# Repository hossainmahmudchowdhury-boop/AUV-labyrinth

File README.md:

# AUV-labyrinth

#### Outlook

This project is about an underwater submarine that can follow a route to survey the aquatic environment. It can detect the number of fish in an area and observe aquatic biology. In this project, it emphasizes an ML-based detection system and a water quality checker.

### PCB 

## Bill of Materials (BOM)

The following table lists the estimated components and costs for the underwater surveillance submarine prototype. The system combines onboard image processing, sensor data collection, underwater imaging, and remote communication.

### 1. Mechanical and PCB Fabrication

| Category | Component | Description | Estimated Cost (USD) |
|---|---|---|---:|
| Mechanical | Waterproof 3D Printing | Custom submarine body | $125.00 |
| PCB Fabrication | Custom Motherboard | Main PCB with replaceable Raspberry Arduino nano headers, power regulation, and sensor interfaces | $58.00 |
| **Subtotal** | | | **$183.00** |

### 2. Electronics and Sensors

| Component | Specification / Purpose | Qty. | Unit Cost (USD) | Total (USD) | Link |
|---|---|---:|---:|---:|---:|
| Servo Motor | Servo rotation control | 6 | $7.40 | $44.40 | [Link](https://shorturl.at/46V4L) |
| Drive Motor | Propulsion | 1 | $46.00 | $46.00 | [Link](https://www.aliexpress.com/item/1005006684228018.html)|
|  CanMV K230 mini AI development board  | Image processing and onboard computing | 1 | $43.37  | $43.37  | [Link](https://www.aliexpress.com/item/1005008934429939.html)|
| Arduino Nano V3.0 Type C  | Sensor interfacing and data acquisition | 1 | $3.00 | $3.00 | [Link](https://www.aliexpress.com/item/1005011889513227.html)|
|  8x8 Thermal Imager Module | Thermal imaging for research | 1 | $32.08  | $32.08  | [Link](https://www.aliexpress.com/item/1005009168490634.html)|
| Gyro Sensor | 3-axis motion and orientation sensing | 1 | $9.51 | $9.51 | [Link](https://www.aliexpress.com/item/1005008666420561.html)|
| Lithium-ion Battery Bundle (20pcs) | Rechargeable power supply | 1 | $22.10 | $22.10 | [Link](https://www.aliexpress.com/item/1005006920168445.html)|
| Extension Cable | 20 m communication/data cable | 1 | $78.70 | $78.70 | [Link](https://www.aliexpress.com/item/1005012780715462.html)|
| Memory Card | 32 GB microSD card | 1 | $10.43  | $10.43  | [Link](https://www.aliexpress.com/item/1005007498167692.html)|
| Light/Infrared Color Spectrometer | Light measurement and spectral analysis | 1 | $8.01 | $8.01 | [Link](https://www.aliexpress.com/item/1005013219123992.html)|
| NEO-M8N GPS Module  |NEO-M8N GPS Module with Built-in Compass for APM PIX Pixhawk PX4|1 | $17.49 | $17.49 |  [Link](https://www.aliexpress.com/item/1005008748794240.html)|
| **Subtotal** | | | | **$315.90** |

### 3. Miscellaneous and Logistics

| Component | Description | Estimated Cost (USD) |
|---|---|---:|
| Passive Components and Hardware | Resistors, capacitors, connectors, and other miscellaneous parts | $15.00 |
| Shipping | Estimated shipping charges | $50.00 |
| **Subtotal** | | **$65.00** |

### 4. Estimated Project Cost

| Category | Estimated Cost (USD) |
|---|---:|
| Mechanical and PCB Fabrication | $183.00 |
| Electronics and Sensors | $315.90 |
| Miscellaneous and Shipping | $65.00 |
| **Total Estimated Cost** | **$563.90** |

> **Note:** All prices are approximate and may vary depending on supplier, availability, shipping, and import duties. Additional waterproof connectors, cable glands, motor drivers, battery protection, and pressure-resistant sealing may increase the final cost if they are not already included.

### 5. Mainboard Design Overview

The custom motherboard is designed around a removable Arduino Nano, connected through headers rather than permanently soldered to the PCB. The board is intended to provide:

- Sensor interfaces using I²C and SPI.
- MicroSD storage interface for sensor readings and other data the Pico can manage.
- USB/UART communication with external equipment.
- Gyroscope interface for motion and stability measurements.
- Motor-driver and servo-control connections.
- 5 V and 3.3 V power regulation.

**Design consideration:**

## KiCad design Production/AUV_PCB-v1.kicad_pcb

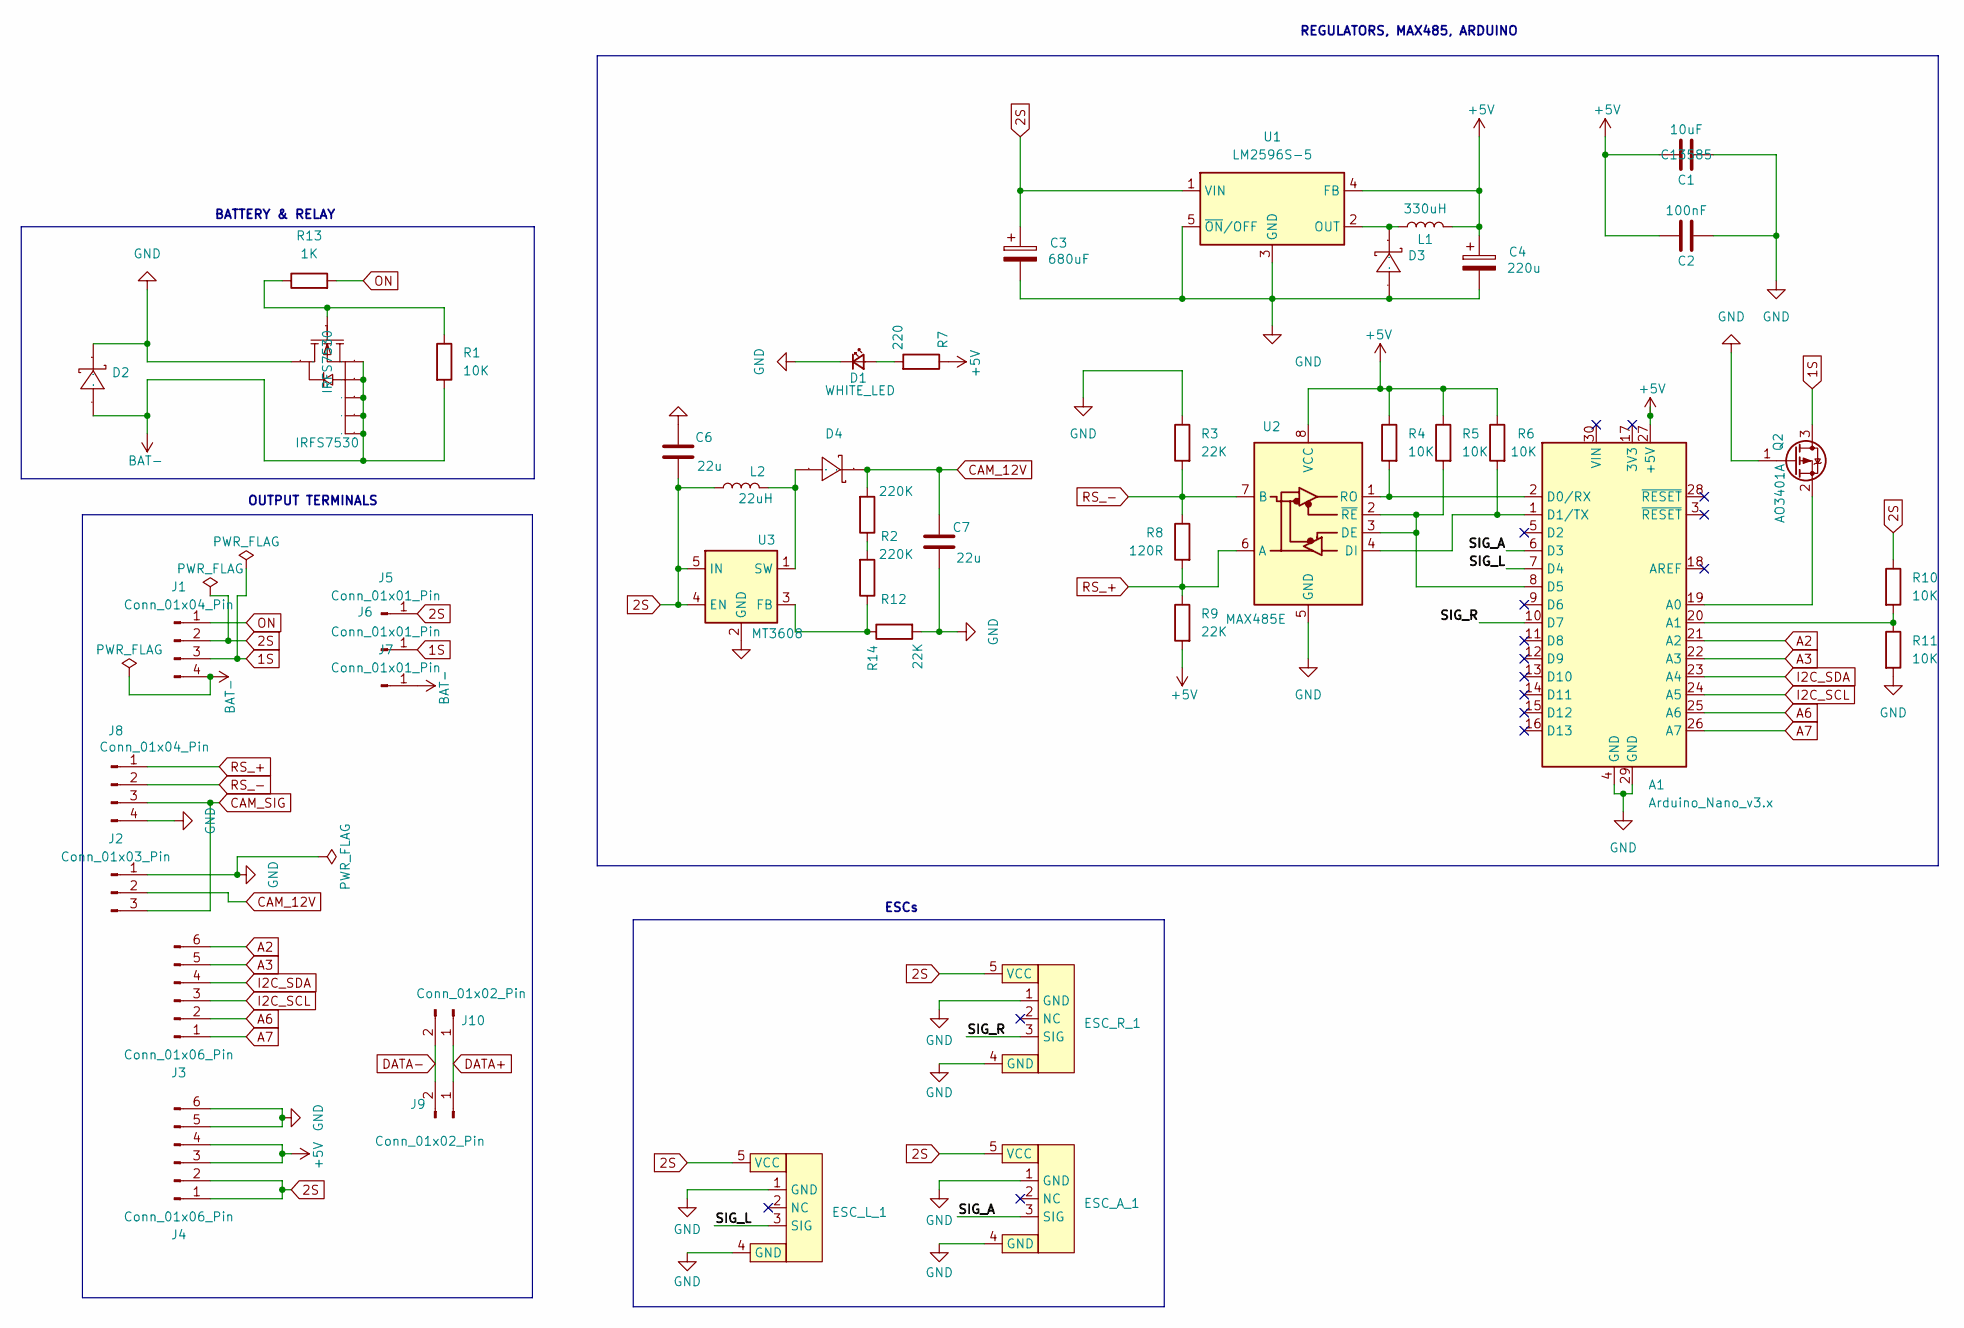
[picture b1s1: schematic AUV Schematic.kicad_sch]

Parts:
A1: Arduino_Nano_v3.x; Arduino_Nano
C1: 10uF; C_1206_3216Metric; LCSC C13585
C2: 100nF; C_0603_1608Metric; LCSC C24497
C3: 680uF; CP_Elec_10x10; LCSC C2980172
C4: 220u; CP_Elec_10x10; LCSC C125977
C6, C7: 22u; C_0805_2012Metric; LCSC C45783
D1: WHITE_LED; LED0603-RED
D2, D3, D4: SMA_L4.4-W2.8-LS5.4-RD; Manufacturer Part SS54; LCSC Part Name 电压:40V 电流:5A
ESC_A_1: ESC_BLHeli (20A), soldering
ESC_L_1: ESC_BLHeli (20A), soldering
ESC_R_1: ESC_BLHeli (20A), soldering
IRFS7530: IRFS7530; IRFS7530-D2PAK-7_L10.6-W9.6-P1.27-LS15.9-BR; LCSC Part Name C445669
J1, J8: Conn_01x04_Pin; PAD4
J2: Conn_01x03_Pin; PAD3
J3, J4: Conn_01x06_Pin; PAD6
J5, J7: Conn_01x01_Pin; Big_charging_pad
J6: Conn_01x01_Pin; small_charging_pad
J9: Conn_01x02_Pin; PAD2
J10: Conn_01x02_Pin; PAD2_rounded
L1: 330uH; L_12x12mm_H8mm; LCSC C10152
L2: 22uH; IND-SMD_L5.0-W3.8 REMOTE; LCSC C177244
Q2: AO3401A; SOT-23
R1: 10K; R_0402_1005Metric
R2: 220K; R_0603_1608Metric; LCSC C25905
R3: 22K; R_0402_1005Metric; LCSC C25768
R4, R5, R6, R10, R11: 10K; R_0402_1005Metric; LCSC C25744
R7: 220; R_0402_1005Metric; LCSC C25905
R8: 120R; R_0402_1005Metric; LCSC C4109
R9: 22K; R_0402_1005Metric
R12: 220K; R_0603_1608Metric; LCSC C4109
R13: 1K; R_0402_1005Metric
R14: 22K; C_0402_1005Metric; LCSC C11702
U1: LM2596S-5; TO-263-5_TabPin3; LCSC C347421
U2: MAX485E; SOIC-8_3.9x4.9mm_P1.27mm; LCSC C481667
U3: MT3608; SOT-23-6; LCSC C84817

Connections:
1S: J1.3, J6.1, Q2.3 (D)
2S: C3.1, C6.2, ESC_A_1.5 (VCC), ESC_L_1.5 (VCC), ESC_R_1.5 (VCC), J1.2, J4.1, J4.2, J5.1, L2.1, R10.1, U1.1 (VIN), U3.4 (EN), U3.5 (IN)
+5V: A1.27 (+5V), C1.1, C2.1, C4.1, J4.3, J4.4, L1.2, R4.1, R5.1, R6.1, R7.1, R9.2, U1.4 (FB), U2.8 (VCC)
/SIG_A: A1.6 (D3), ESC_A_1.3 (SIG)
/SIG_L: A1.7 (D4), ESC_L_1.3 (SIG)
/SIG_R: A1.10 (D7), ESC_R_1.3 (SIG)
A2: A1.21 (A2), J3.6
A3: A1.22 (A3), J3.5
A6: A1.25 (A6), J3.2
A7: A1.26 (A7), J3.1
BAT-: D2.2 (A), IRFS7530.2 (S), IRFS7530.3 (S), IRFS7530.5 (S), IRFS7530.6 (S), IRFS7530.7 (S), J1.4, J7.1, R1.2
CAM_12V: C7.1, D4.1 (K), J2.2, R2.2
CAM_SIG: J2.3, J8.3
DATA+: J9.1, J10.1
DATA-: J9.2, J10.2
GND: A1.4 (GND), A1.29 (GND), C1.2, C2.2, C3.2, C4.2, C6.1, C7.2, D1.1 (K), D2.1 (K), D3.2 (A), ESC_A_1.1 (GND), ESC_A_1.4 (GND), ESC_L_1.1 (GND), ESC_L_1.4 (GND), ESC_R_1.1 (GND), ESC_R_1.4 (GND), IRFS7530.4 (D), J2.1, J4.5, J4.6, J8.4, Q2.1 (G), R3.1, R11.2, R14.2, U1.3 (GND), U1.5 (~ON/OFF), U2.5 (GND), U3.2 (GND)
I2C_SCL: A1.24 (A5), J3.3
I2C_SDA: A1.23 (A4), J3.4
unnamed: A1.19 (A0), Q2.2 (S)
unnamed: A1.20 (A1), R10.2, R11.1
unnamed: A1.2 (D0/RX), R4.2, U2.1 (RO)
unnamed: A1.1 (D1/TX), R6.2, U2.4 (DI)
unnamed: A1.8 (D5), R5.2, U2.2 (~RE), U2.3 (DE)
unnamed: D1.2 (A), R7.2
unnamed: D3.1 (K), L1.1, U1.2 (OUT)
unnamed: D4.2 (A), L2.2, U3.1 (SW)
unnamed: IRFS7530.1 (G), R1.1, R13.1
unnamed: R2.1, R12.2
unnamed: R12.1, R14.1, U3.3 (FB)
ON: J1.1, R13.2
RS_+: J8.1, R8.2, R9.1, U2.6 (A)
RS_-: J8.2, R3.2, R8.1, U2.7 (B)

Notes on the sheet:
REGULATORS, MAX485, ARDUINO
BATTERY & RELAY
ESCs
OUTPUT TERMINALS

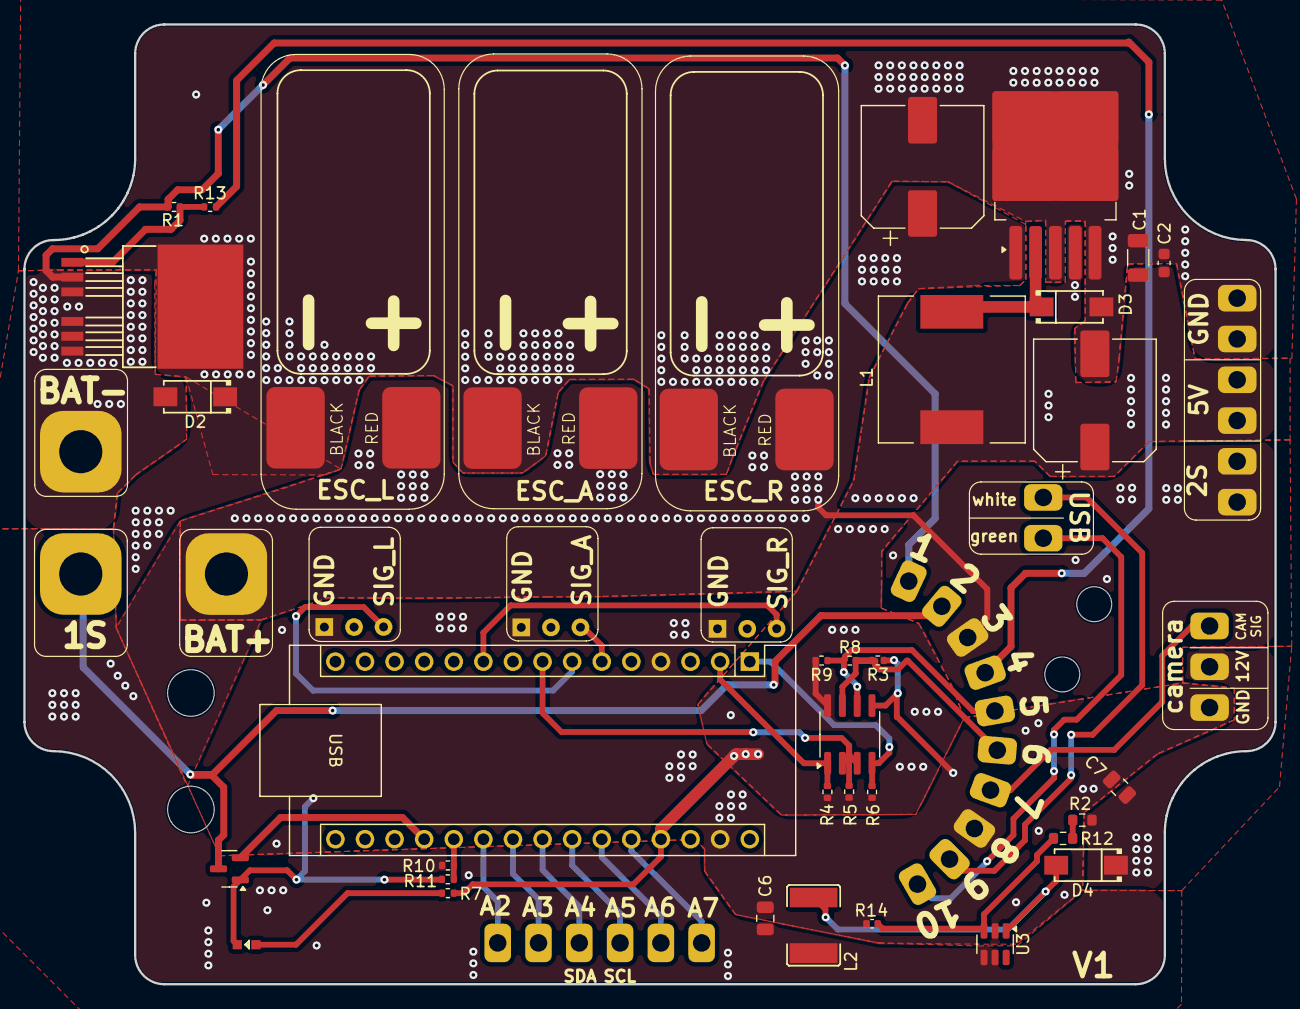
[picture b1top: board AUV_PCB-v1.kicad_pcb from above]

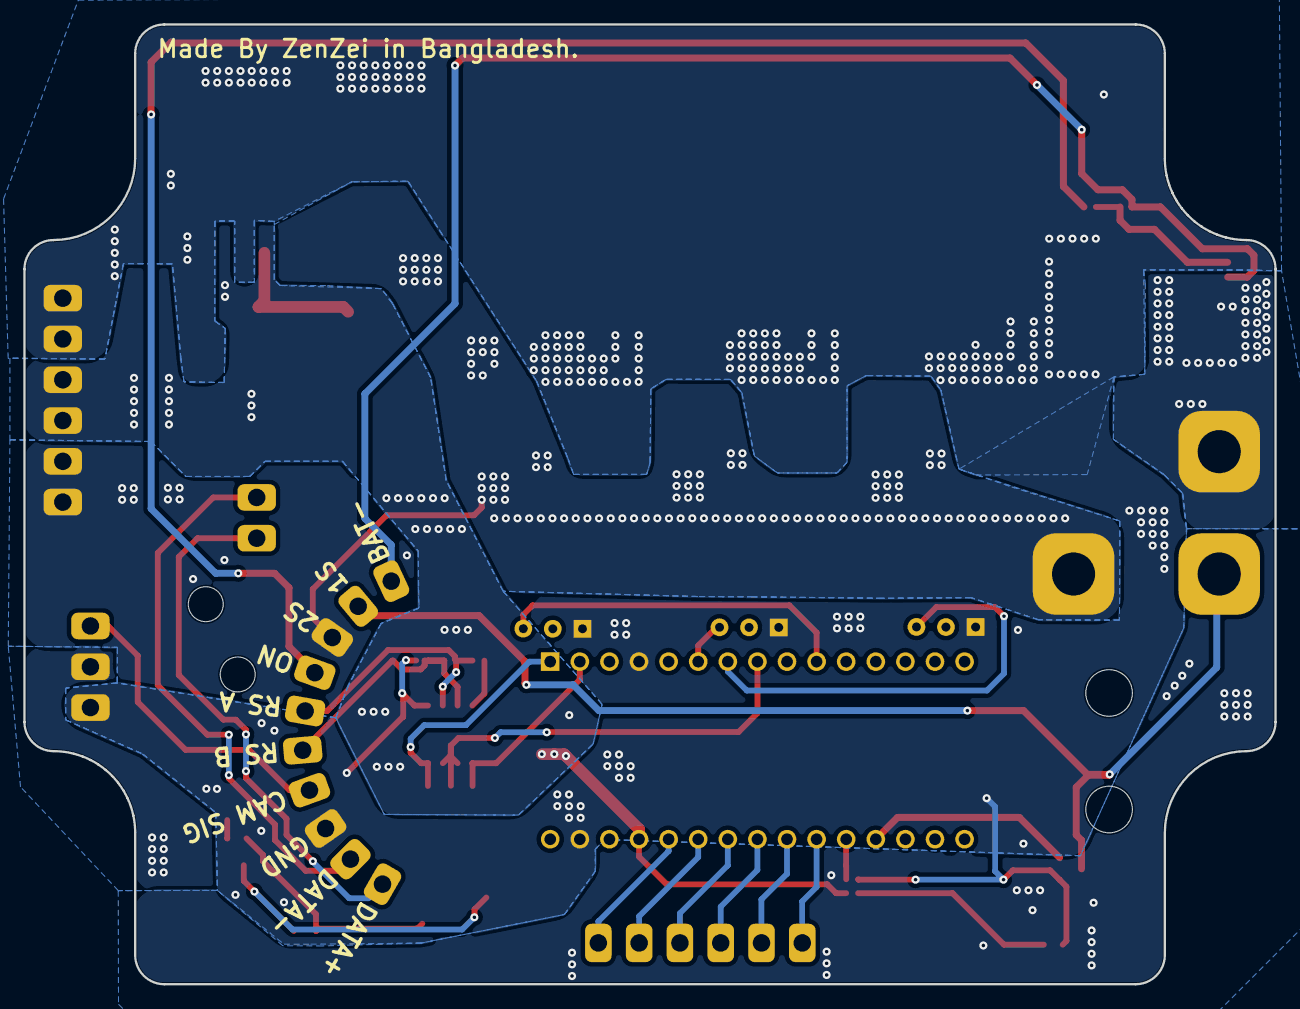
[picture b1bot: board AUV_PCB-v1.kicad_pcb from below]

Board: 2 copper layers, 107.4 x 82.4 mm, 45 parts (2 on the bottom side), 32 nets.
